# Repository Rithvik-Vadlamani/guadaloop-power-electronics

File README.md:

# Guadaloop power electronics

Selected power electronics designs from my work on Guadaloop. This repository collects editable schematics and PCB layouts so the designs can be reviewed without digging through unrelated project files.

| Design | What it covers | Files |
| --- | --- | --- |
| Levitation H-bridge | A nominal 60 V bidirectional coil-driver channel, including gate driving and current sensing. | [Design and review notes](levitation-hbridge/README.md) |
| 60 V to 24 V buck converter | A buck-converter design with a 10 A output target. | [Editable design](buck-60v-24v/) |
| Medium-voltage board, Rev F1 | A compact prototype power-board revision with revised inductance, compensation, and thermal copper. | [Design notes](medium-voltage-revf1/README.md) |

These are engineering designs and review packages. Their voltage/current targets are design requirements; the included files do not establish measured hardware performance.

My broader team work includes power distribution, PCB assembly, and enclosure work. This repository contains the design files located for this publication. It does not include every team design or claim sole authorship of collaborative work.

For my wireless power transfer models and results, see [the separate wireless power repository](https://github.com/Rithvik-Vadlamani/guadaloop-wireless-power-transfer).

## Open the designs

Use KiCad with the standard symbol and footprint libraries installed. Each folder contains its own project and local library tables. Start with the `.kicad_pro` file. Some projects were saved with KiCad 10; the levitation design requires KiCad 10.0.3 or later.

Saved review results describe the revision and assumptions recorded in each package. Native design files are the source of truth. No fabrication or hardware testing was performed as part of publishing this repository.

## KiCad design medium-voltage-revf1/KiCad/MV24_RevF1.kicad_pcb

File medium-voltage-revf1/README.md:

# MV24 Rev F1 — compact prototype candidate

Rev F1 implements the agreed minimal-change revisions to Rev F, except precharge. It preserves the original CSD19532Q5BT MOSFETs, all component positions, connector positions, mounting holes and board outline. Rev F is preserved separately. No board has been built or tested.

## What changed

| Item | Rev F | Rev F1 | Purpose |
|---|---|---|---|
| L1 | 10 µH, CPRX3231L-100MC | 15 µH, CPRX3231L-150MC | Coordinate inductance with the reduced switching frequency to limit ripple. Same package family and placement; revised terminal slots. |
| R6 | 75 kΩ | 100 kΩ, RT0805BRD07100KL | Reduce nominal switching frequency from approximately 133 kHz to 100 kHz, reducing gate-drive demand and frequency-dependent losses. |
| R10 | 6.81 kΩ | 8.2 kΩ, RC0805FR-078K2L | Retune compensation for the revised power stage. C26 remains 3.3 nF. |
| Copper | 35/15.2/15.2/35 µm | 70/35/35/70 µm | Improve conduction and heat spreading without enlarging the board. |
| MOSFET cooling paths | Original copper and vias | Local VIN copper extended, small bottom SW island, 37 additional thermal vias | Transfer heat away from the existing MOSFET packages. |
| Surface finish | OSP | ENIG | Flat assembly surface compatible with the specified filled-and-capped in-pad via process. |

There are still **51 fitted electronic/connector parts: three substitutions, zero added fitted parts**. The 63 PCB footprints also include six test points, four mounting holes and two unpopulated snubber positions. Vias are board features, not additional BOM components. External cooling equipment is separate from that count.

## Files

- `KiCad/MV24_RevF1.kicad_pro`: native editable project with local libraries/models.
- `Procurement/BOM.csv`: updated exact-part prototype BOM. Prices and availability have not been refreshed; this is not a purchase-ready quotation.
- `Documentation/Board.png` and `Documentation/Schematic.png`: reviewed previews.
- `Documentation/Engineering-notes.md`: design rationale, calculation scope and remaining uncertainties.
- `Documentation/Fabrication-and-test.md`: required PCB process, cooling fixture and staged test plan.
- `Verification/final-native/`: final ERC, DRC, native netlists and independent connectivity reports.
- `Verification/final-audit.json`: unchanged-layout/MOSFET/BOM comparison and report freshness checks.
- `Manufacturing/`: reviewed four-layer Gerbers, plated/non-plated drills, fabrication requirements and a selective filled-via map.
- `Assembly/`: reconciled 51-part BOM/placements, labeled assembly drawing and populated-variant stencil artwork with process-review instructions.

## Status

Native KiCad 10.0.3 ERC and DRC pass with no reported violations, unconnected items or schematic parity findings. Independent schematic/PCB connectivity and pad-map checks pass. All 154 tracked baseline files are unchanged. These checks establish consistency and routing-rule compliance, not power performance or safety qualification.

The averaged loop screen supports the chosen compensation as a prototype candidate. Thermal screening still indicates substantial heating and sensitivity to airflow/model resolution. **Continuous 24 V / 20 A operation is a design target, not an established rating.**

Precharge and the associated battery connection/fusing decisions are intentionally deferred as a separate scope. Do not directly hot-plug the battery into this candidate. The board-only fabrication/assembly handoff is prepared independently for fabricator DFM and a supervised bench prototype; it does not wait for a battery-interface redesign. Vendor process acceptance and assembler stencil/orientation review remain required before ordering. No hardware-performance or battery-use release is implied.

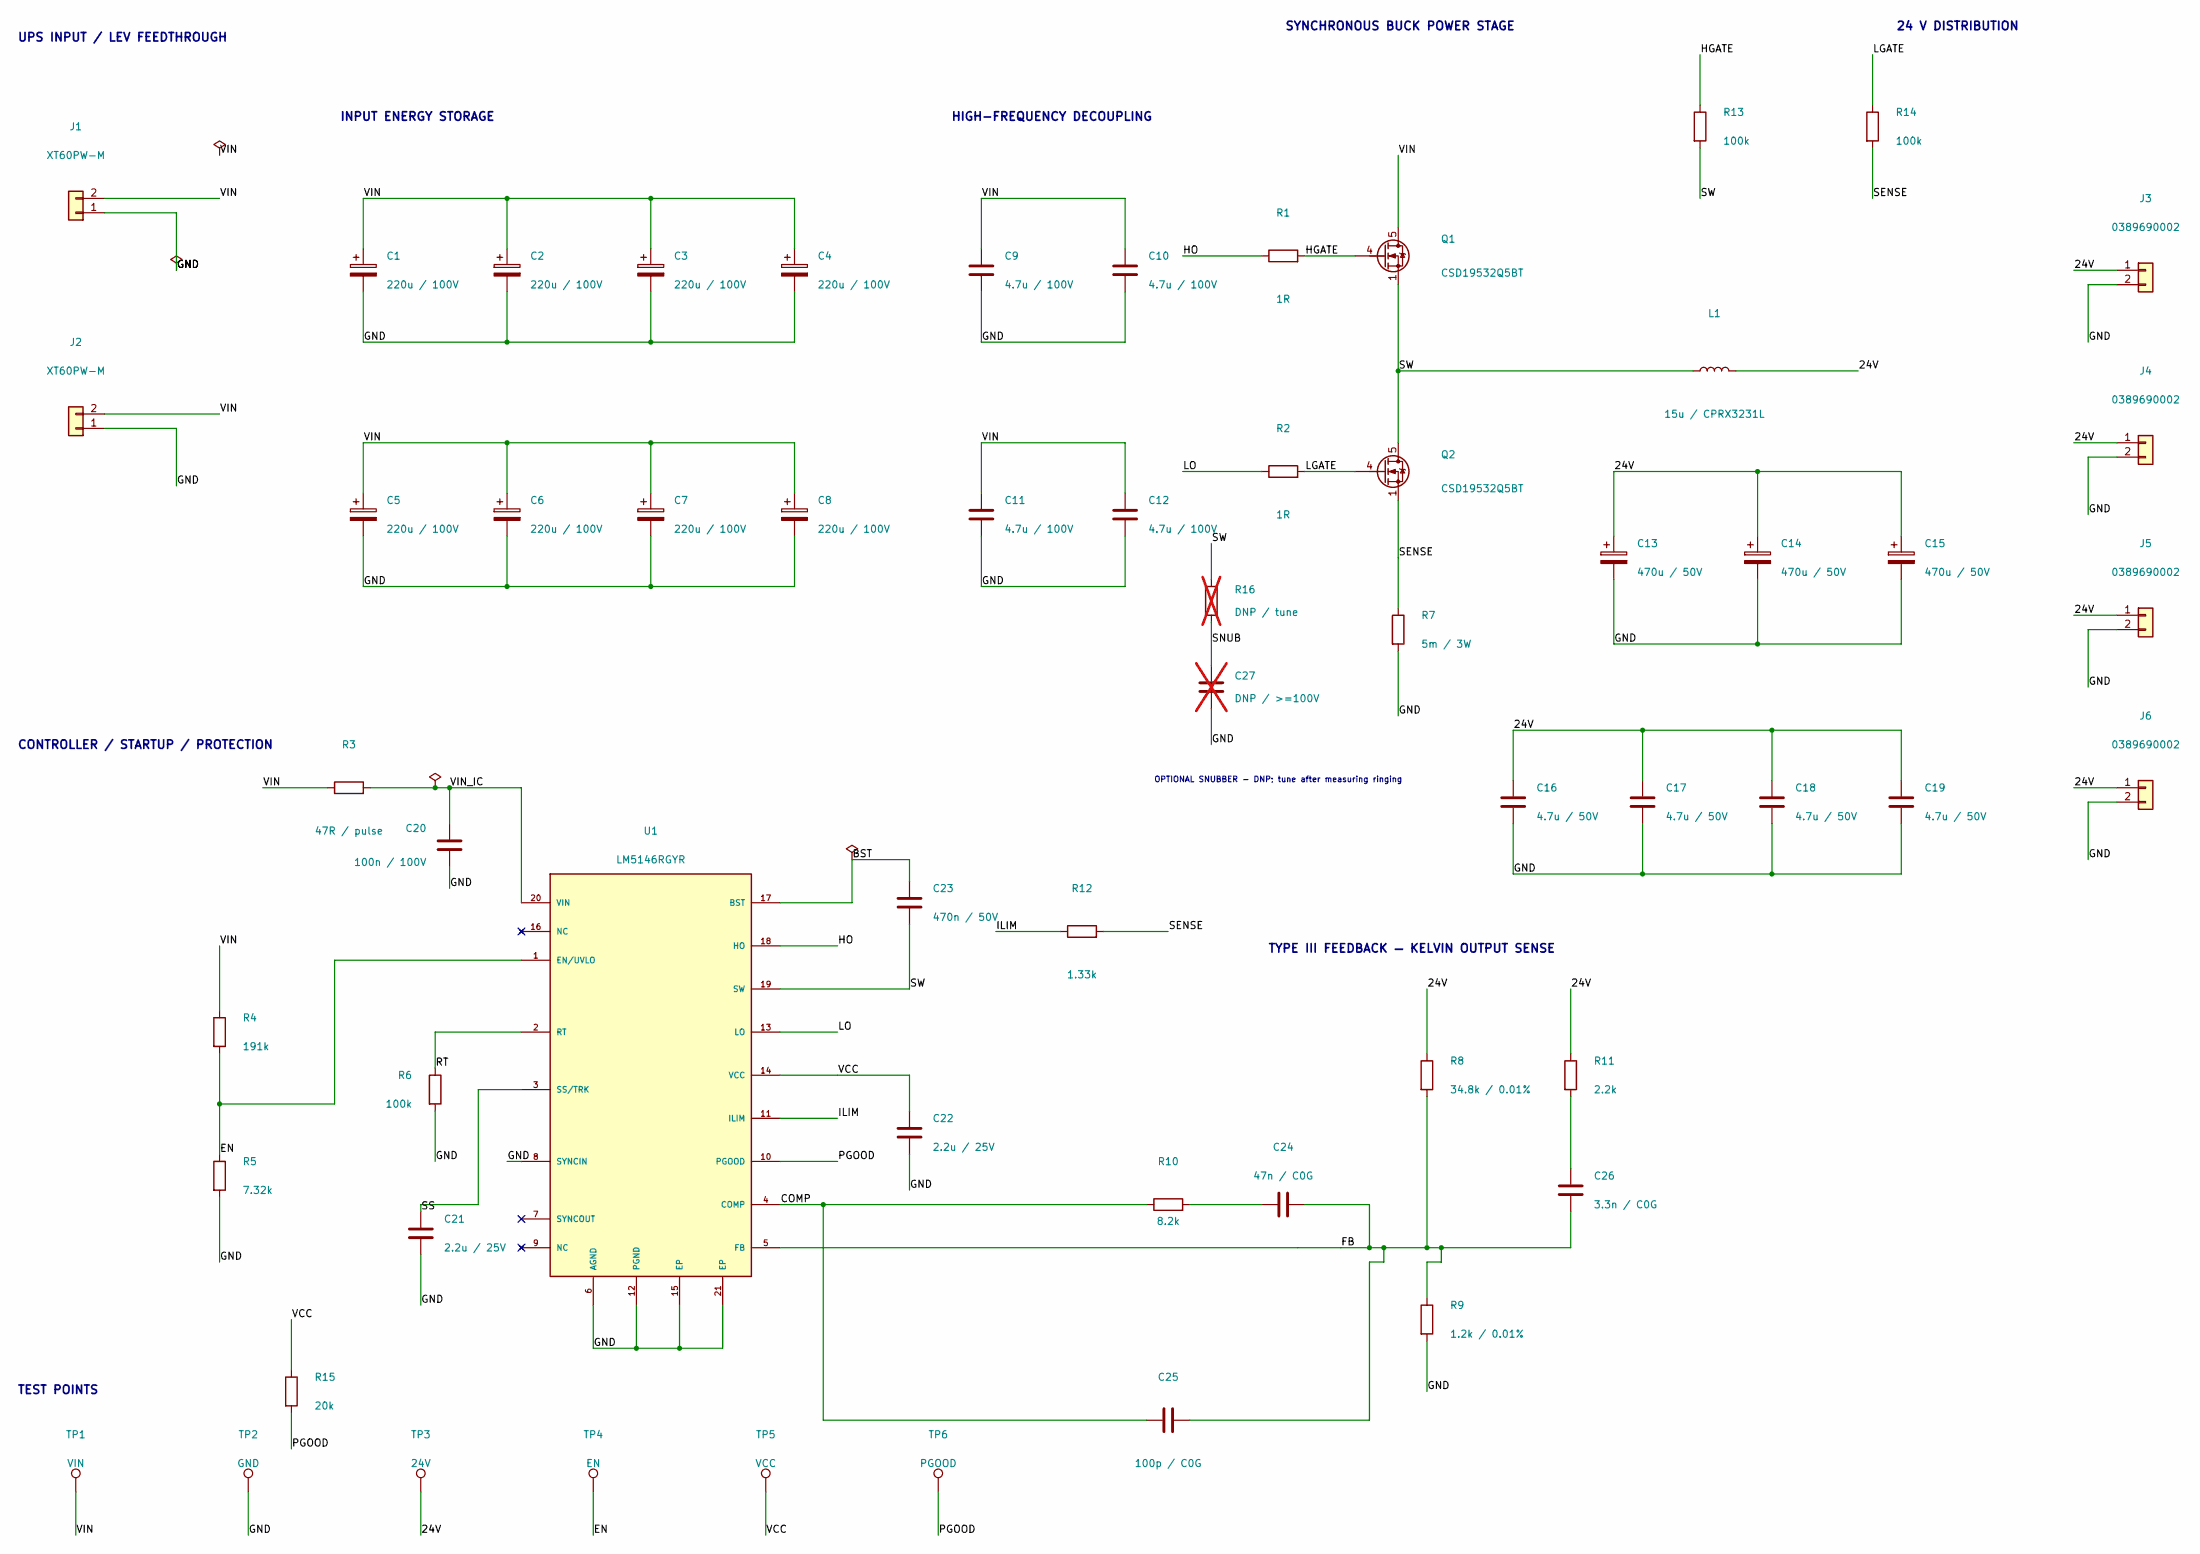
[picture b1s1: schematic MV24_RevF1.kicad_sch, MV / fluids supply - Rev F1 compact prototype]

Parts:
C1, C2, C3, C4, C5, C6, C7, C8: 220u / 100V; CP_Radial_D12.5mm_P5.00mm; MPN EEU-FS2A221B
C9, C10, C11, C12: 4.7u / 100V; C_1812_4532Metric; MPN KGM43JR72A475KV
C13, C14, C15: 470u / 50V; CP_Radial_D12.5mm_P5.00mm; MPN EEU-FR1H471B
C16, C17, C18, C19: 4.7u / 50V; C_1206_3216Metric; MPN GRM31CR71H475KA12L
C20: 100n / 100V; C_0805_2012Metric; MPN C0805C104K1RACTU
C21, C22: 2.2u / 25V; C_0805_2012Metric; MPN C0805C225K3RACTU
C23: 470n / 50V; C_0805_2012Metric; MPN C0805C474K5RACTU
C24: 47n / C0G; C_1206_3216Metric; MPN C1206C473J5GACTU
C25: 100p / C0G; C_0805_2012Metric; MPN C0805C101J5GACTU
C26: 3.3n / C0G; C_0805_2012Metric; MPN C0805C332J5GACTU
C27: DNP / >=100V; C_1206_3216Metric; not fitted
J1, J2: XT60PW-M; AMASS_XT60PW-M_1x02_P7.20mm_Horizontal; MPN XT60PW-M
J3, J4, J5, J6: 0389690002; Molex_0389690002; MPN 0389690002
L1: 15u / CPRX3231L; CODACA_CPRX3231L_150MC; MPN CPRX3231L-150MC
Q1, Q2: CSD19532Q5BT; TI_Q5B_5x6; MPN CSD19532Q5BT
R1, R2: 1R; R_0805_2012Metric; MPN RC0805FR-071RL
R3: 47R / pulse; R_0805_2012Metric; MPN CRCW080547R0FKEAHP
R4: 191k; R_0805_2012Metric; MPN RC0805FR-07191KL
R5: 7.32k; R_0805_2012Metric; MPN RC0805FR-077K32L
R6: 100k; R_0805_2012Metric; MPN RT0805BRD07100KL
R7: 5m / 3W; Bourns_CRE2512_R005; MPN CRE2512-FZ-R005E-3
R8: 34.8k / 0.01%; R_0805_2012Metric; MPN RT0805LRA0734K8L
R9: 1.2k / 0.01%; R_0805_2012Metric; MPN RT0805LRA071K2L
R10: 8.2k; R_0805_2012Metric; MPN RC0805FR-078K2L
R11: 2.2k; R_0805_2012Metric; MPN RC0805FR-072K2L
R12: 1.33k; R_0805_2012Metric; MPN RT0805BRD071K33L
R13, R14: 100k; R_0805_2012Metric; MPN RC0805FR-07100KL
R15: 20k; R_0805_2012Metric; MPN RC0805FR-0720KL
R16: DNP / tune; R_1206_3216Metric; not fitted
TP1: VIN; TestPoint_Pad_D2.0mm
TP2: GND; TestPoint_Pad_D2.0mm
TP3: 24V; TestPoint_Pad_D2.0mm
TP4: EN; TestPoint_Pad_D2.0mm
TP5: VCC; TestPoint_Pad_D2.0mm
TP6: PGOOD; TestPoint_Pad_D2.0mm
U1: LM5146RGYR; TI_RGY0020B; MPN LM5146RGYR

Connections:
/24V: C13.1, C14.1, C15.1, C16.1, C17.1, C18.1, C19.1, J3.1, J4.1, J5.1, J6.1, L1.2, R8.1, R11.1, TP3.1
/BST: C23.1, U1.17 (BST)
/COMP: C25.1, R10.1, U1.4 (COMP)
/EN: R4.2, R5.1, TP4.1, U1.1 (EN/UVLO)
/FB: C24.2, C25.2, C26.2, R8.2, R9.1, U1.5 (FB)
/GND: C1.2, C2.2, C3.2, C4.2, C5.2, C6.2, C7.2, C8.2, C9.2, C10.2, C11.2, C12.2, C13.2, C14.2, C15.2, C16.2, C17.2, C18.2, C19.2, C20.2, C21.2, C22.2, C27.2, J1.1, J2.1, J3.2, J4.2, J5.2, J6.2, R5.2, R6.2, R7.2, R9.2, TP2.1, U1.6 (AGND), U1.8 (SYNCIN), U1.12 (PGND), U1.15 (EP), U1.21 (EP)
/HGATE: Q1.4 (G), R1.2, R13.1
/HO: R1.1, U1.18 (HO)
/ILIM: R12.1, U1.11 (ILIM)
/LGATE: Q2.4 (G), R2.2, R14.1
/LO: R2.1, U1.13 (LO)
/PGOOD: R15.2, TP6.1, U1.10 (PGOOD)
/RT: R6.1, U1.2 (RT)
/SENSE: Q2.1 (S), Q2.2 (S), Q2.3 (S), R7.1, R12.2, R14.2
/SNUB: C27.1, R16.2
/SS: C21.1, U1.3 (SS/TRK)
/SW: C23.2, L1.1, Q1.1 (S), Q1.2 (S), Q1.3 (S), Q2.5 (D), R13.2, R16.1, U1.19 (SW)
/VCC: C22.1, R15.1, TP5.1, U1.14 (VCC)
/VIN: C1.1, C2.1, C3.1, C4.1, C5.1, C6.1, C7.1, C8.1, C9.1, C10.1, C11.1, C12.1, J1.2, J2.2, Q1.5 (D), R3.1, R4.1, TP1.1
/VIN_IC: C20.1, R3.2, U1.20 (VIN)
unnamed: C24.1, R10.2
unnamed: C26.1, R11.2

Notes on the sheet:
UPS INPUT / LEV FEEDTHROUGH
INPUT ENERGY STORAGE
HIGH-FREQUENCY DECOUPLING
SYNCHRONOUS BUCK POWER STAGE
24 V DISTRIBUTION
CONTROLLER / STARTUP / PROTECTION
TYPE III FEEDBACK — KELVIN OUTPUT SENSE
TEST POINTS
OPTIONAL SNUBBER - DNP; tune after measuring ringing

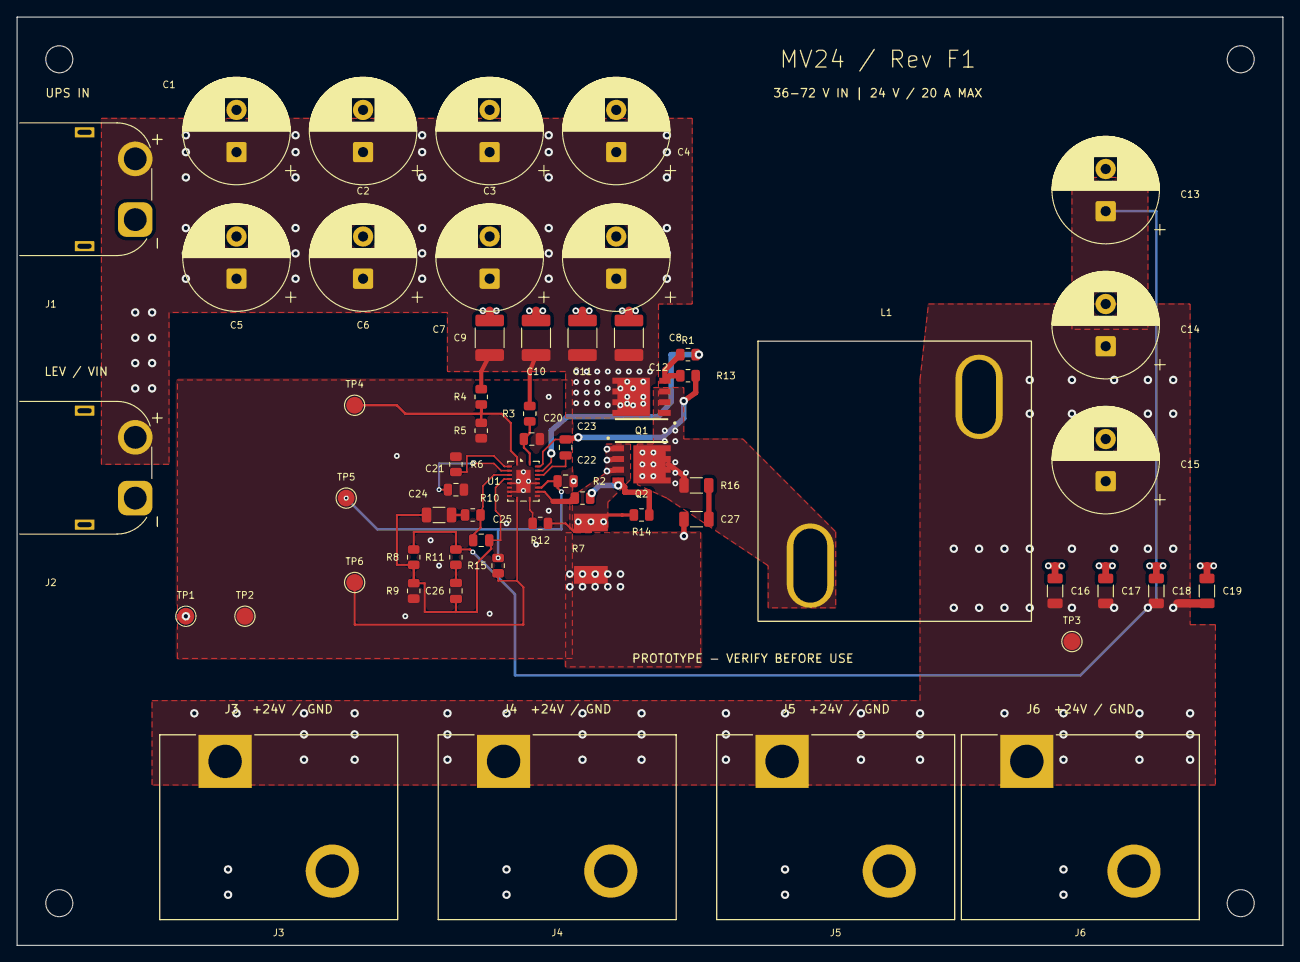
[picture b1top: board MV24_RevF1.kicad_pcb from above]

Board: 4 copper layers, 150.0 x 110.0 mm, 63 parts (0 on the bottom side), 22 nets.

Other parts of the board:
H1, H2, H3, H4: M3 clearance; MountingHole_3.2mm_M3

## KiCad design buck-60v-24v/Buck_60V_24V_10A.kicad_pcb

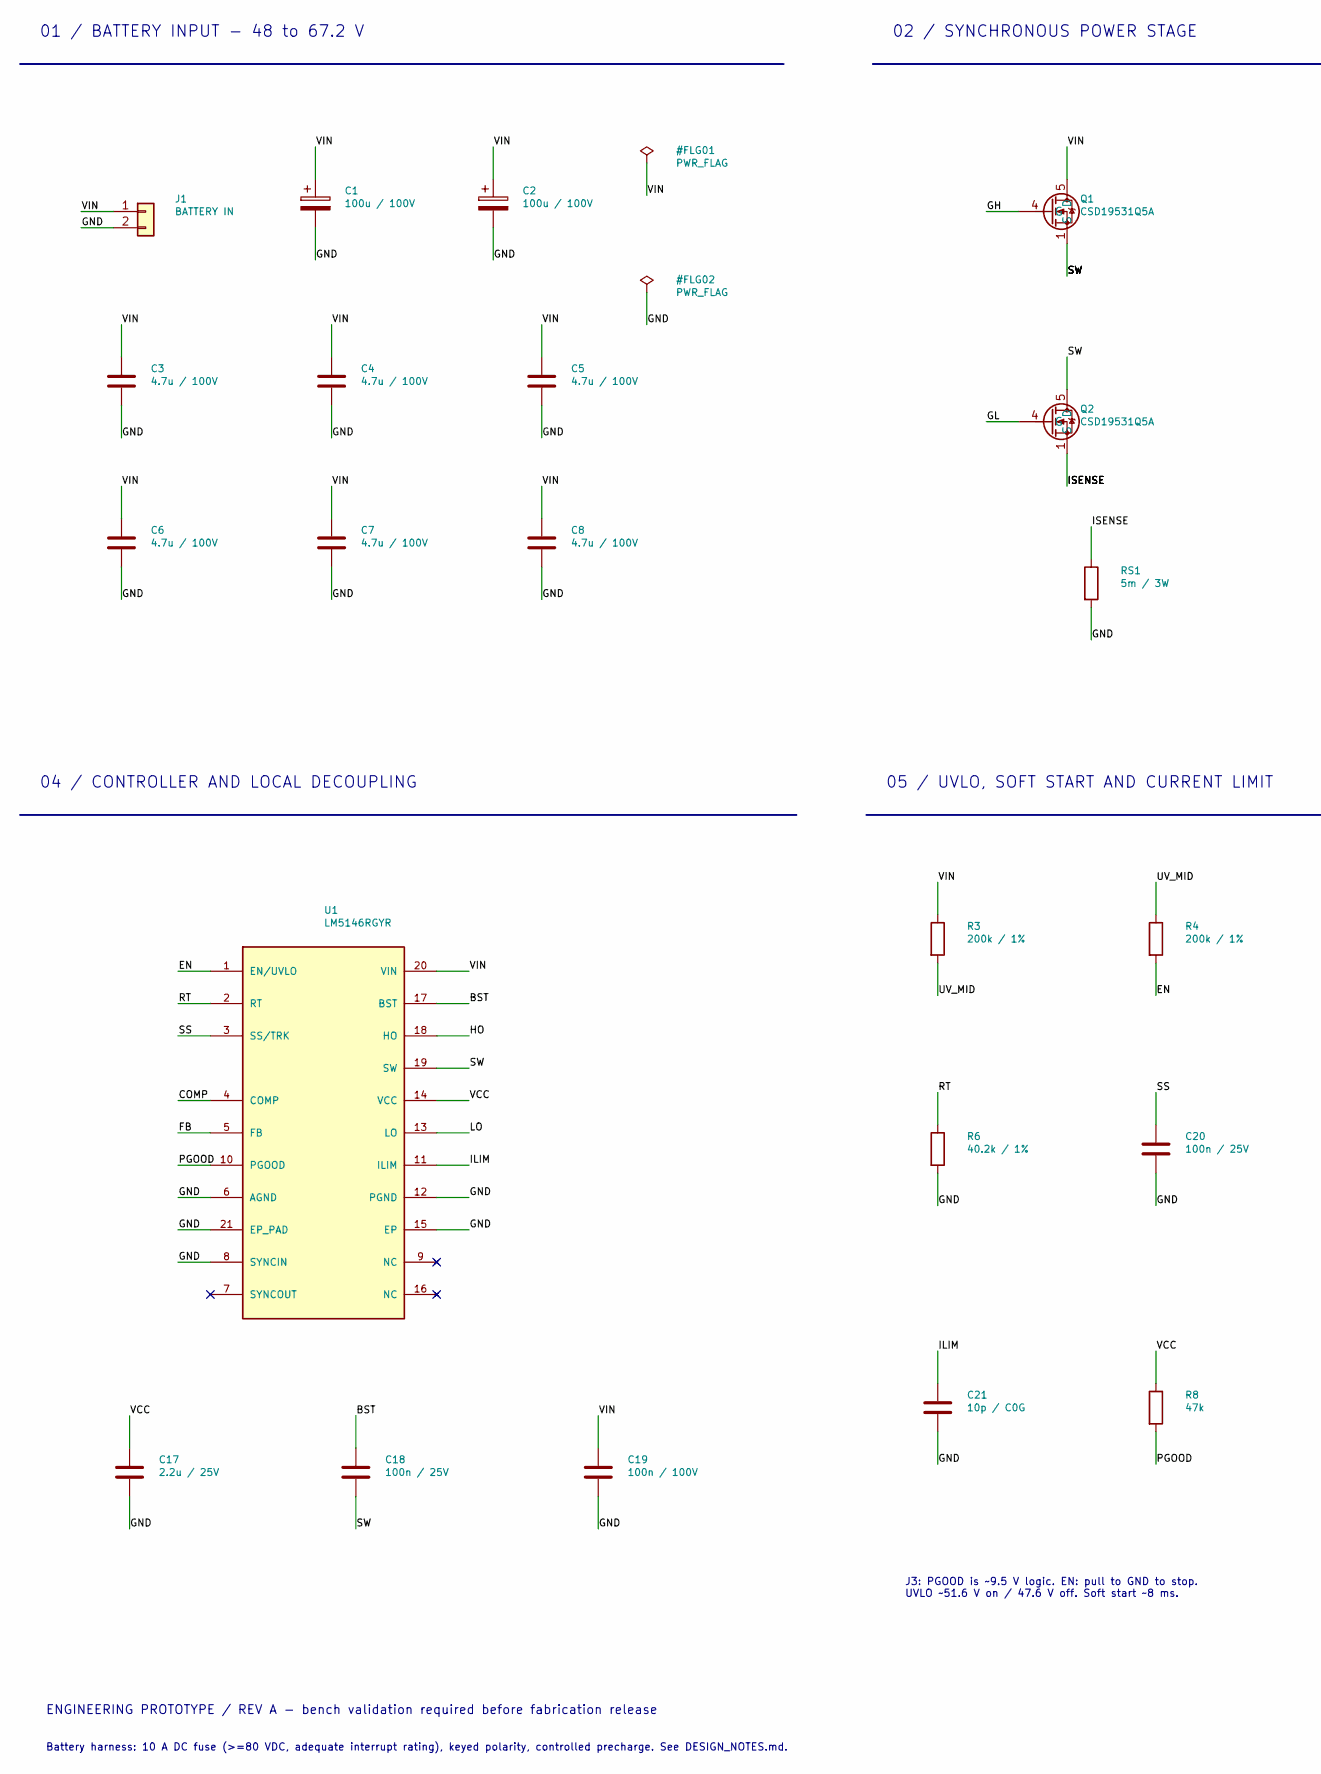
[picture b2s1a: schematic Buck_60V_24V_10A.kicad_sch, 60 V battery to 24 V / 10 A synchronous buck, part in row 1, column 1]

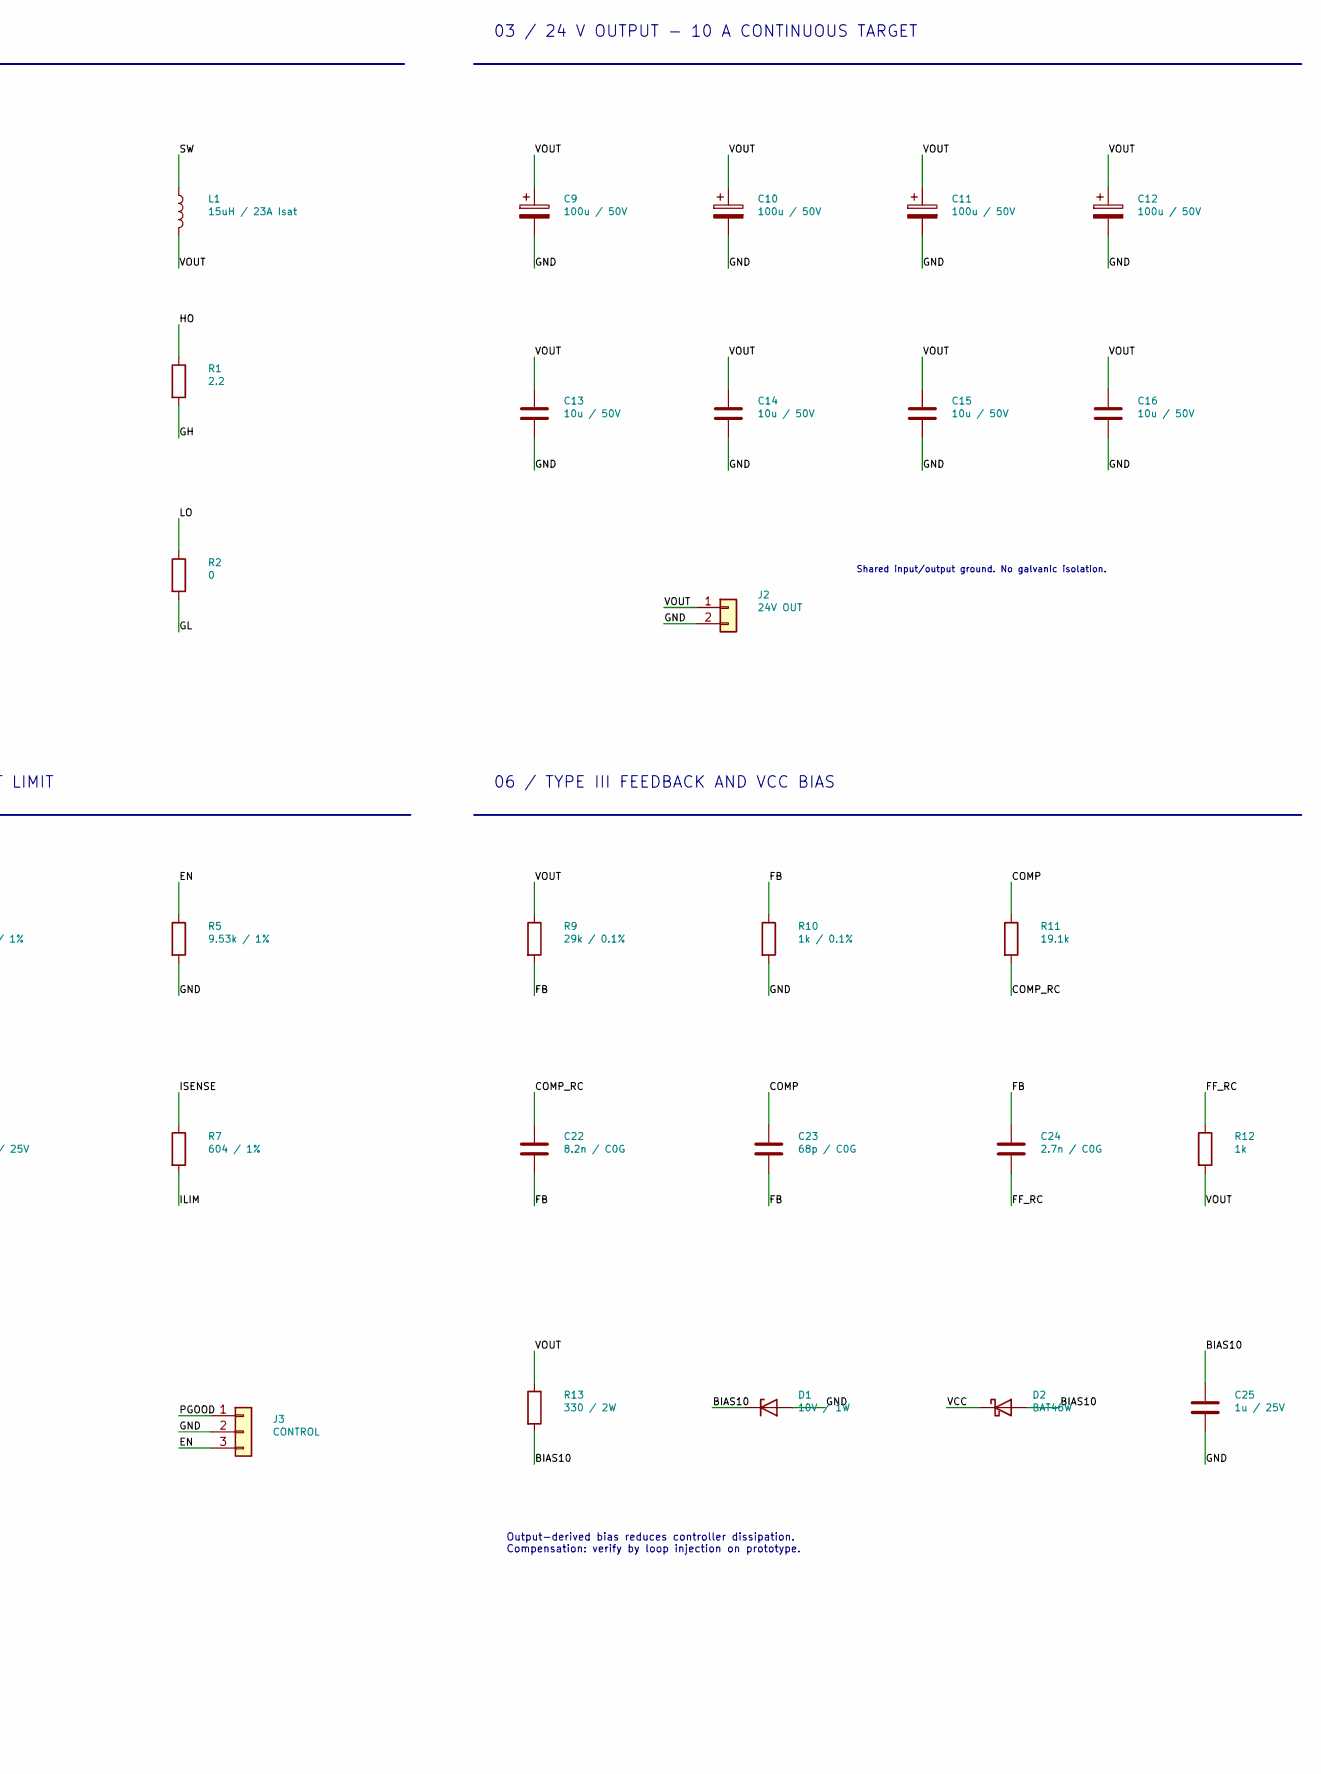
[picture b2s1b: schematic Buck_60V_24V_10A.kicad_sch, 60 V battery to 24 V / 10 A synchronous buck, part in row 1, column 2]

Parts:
C1, C2: 100u / 100V; CP_Radial_D10.0mm_P5.00mm; MPN EEU-FR2A101
C3, C4, C5, C6, C7, C8: 4.7u / 100V; C_1210_3225Metric; MPN CGA6M3X7S2A475K200AB
C9, C10, C11, C12: 100u / 50V; C_Elec_10x10.2; MPN EEH-ZE1H101P
C13, C14, C15, C16: 10u / 50V; C_1210_3225Metric; MPN GRM32ER71H106KA12L
C17: 2.2u / 25V; C_0805_2012Metric; MPN GRM21BR71E225KA73L
C18, C20: 100n / 25V; C_0603_1608Metric; MPN GRM188R71E104KA01D
C19: 100n / 100V; C_0805_2012Metric; MPN GRM21BR72A104KAC4L
C21: 10p / C0G; C_0603_1608Metric; MPN GRM1885C1H100JA01D
C22: 8.2n / C0G; C_0603_1608Metric; MPN GRM1885C1H822JA01D
C23: 68p / C0G; C_0603_1608Metric; MPN GRM1885C1H680JA01D
C24: 2.7n / C0G; C_0603_1608Metric; MPN GRM1885C1H272JA01D
C25: 1u / 25V; C_0805_2012Metric; MPN GRM21BR71E105KA99L
D1: 10V / 1W; D_SMA; MPN SMAZ10-13-F
D2: BAT46W; D_SOD-123; MPN BAT46W-7-F
J1: BATTERY IN; AMASS_XT60PW-M_1x02_P7.20mm_Horizontal; MPN XT60PW-M
J2: 24V OUT; AMASS_XT60PW-F_1x02_P7.20mm_Horizontal; MPN XT60PW-F
J3: CONTROL; PinHeader_1x03_P2.54mm_Vertical; MPN Pin header 1x3 2.54mm
L1: 15uH / 23A Isat; L_Coilcraft_XAL1510-153; MPN XAL1510-153MED
Q1, Q2: CSD19531Q5A; TDSON-8-1; MPN CSD19531Q5A
R1: 2.2; R_0603_1608Metric; MPN RC0603FR-072R2L
R2: 0; R_0603_1608Metric; MPN RC0603JR-070RL
R3, R4: 200k / 1%; R_0603_1608Metric; MPN RC0603FR-07200KL
R5: 9.53k / 1%; R_0603_1608Metric; MPN RC0603FR-079K53L
R6: 40.2k / 1%; R_0603_1608Metric; MPN RC0603FR-0740K2L
R7: 604 / 1%; R_0603_1608Metric; MPN RC0603FR-07604RL
R8: 47k; R_0603_1608Metric; MPN RC0603FR-0747KL
R9: 29k / 0.1%; R_0603_1608Metric; MPN TNPW060329K0BEEA
R10: 1k / 0.1%; R_0603_1608Metric; MPN TNPW06031K00BEEA
R11: 19.1k; R_0603_1608Metric; MPN RC0603FR-0719K1L
R12: 1k; R_0603_1608Metric; MPN RC0603FR-071KL
R13: 330 / 2W; R_2512_6332Metric; MPN CRCW2512330RJNEGHP
RS1: 5m / 3W; R_2512_6332Metric; MPN WSLP25125L000FEA
U1: LM5146RGYR; LM5146_RGY0020B; MPN LM5146RGYR

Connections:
BIAS10: C25.1, D1.1 (K), D2.2 (A), R13.2
BST: C18.1, U1.17 (BST)
COMP: C23.1, R11.1, U1.4 (COMP)
COMP_RC: C22.1, R11.2
EN: J3.3, R4.2, R5.1, U1.1 (EN/UVLO)
FB: C22.2, C23.2, C24.1, R9.2, R10.1, U1.5 (FB)
FF_RC: C24.2, R12.1
GH: Q1.4 (G), R1.2
GL: Q2.4 (G), R2.2
GND: C1.2, C2.2, C3.2, C4.2, C5.2, C6.2, C7.2, C8.2, C9.2, C10.2, C11.2, C12.2, C13.2, C14.2, C15.2, C16.2, C17.2, C19.2, C20.2, C21.2, C25.2, D1.2 (A), J1.2, J2.2, J3.2, R5.2, R6.2, R10.2, RS1.2, U1.6 (AGND), U1.8 (SYNCIN), U1.12 (PGND), U1.15 (EP), U1.21 (EP_PAD)
HO: R1.1, U1.18 (HO)
ILIM: C21.1, R7.2, U1.11 (ILIM)
ISENSE: Q2.1 (S), Q2.2 (S), Q2.3 (S), R7.1, RS1.1
LO: R2.1, U1.13 (LO)
PGOOD: J3.1, R8.2, U1.10 (PGOOD)
RT: R6.1, U1.2 (RT)
SS: C20.1, U1.3 (SS/TRK)
SW: C18.2, L1.1, Q1.1 (S), Q1.2 (S), Q1.3 (S), Q2.5 (D), U1.19 (SW)
UV_MID: R3.2, R4.1
VCC: C17.1, D2.1 (K), R8.1, U1.14 (VCC)
VIN: C1.1, C2.1, C3.1, C4.1, C5.1, C6.1, C7.1, C8.1, C19.1, J1.1, Q1.5 (D), R3.1, U1.20 (VIN)
VOUT: C9.1, C10.1, C11.1, C12.1, C13.1, C14.1, C15.1, C16.1, J2.1, L1.2, R9.1, R12.2, R13.1

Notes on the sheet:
06 / TYPE III FEEDBACK AND VCC BIAS
ENGINEERING PROTOTYPE / REV A - bench validation required before fabrication release
01 / BATTERY INPUT - 48 to 67.2 V
04 / CONTROLLER AND LOCAL DECOUPLING
Output-derived bias reduces controller dissipation. Compensation: verify by loop injection on prototype.
03 / 24 V OUTPUT - 10 A CONTINUOUS TARGET
02 / SYNCHRONOUS POWER STAGE
Shared input/output ground. No galvanic isolation.
J3: PGOOD is ~9.5 V logic. EN: pull to GND to stop. UVLO ~51.6 V on / 47.6 V off. Soft start ~8 ms.
05 / UVLO, SOFT START AND CURRENT LIMIT
Battery harness: 10 A DC fuse (>=80 VDC, adequate interrupt rating), keyed polarity, controlled precharge. See DESIGN_NOTES.md.

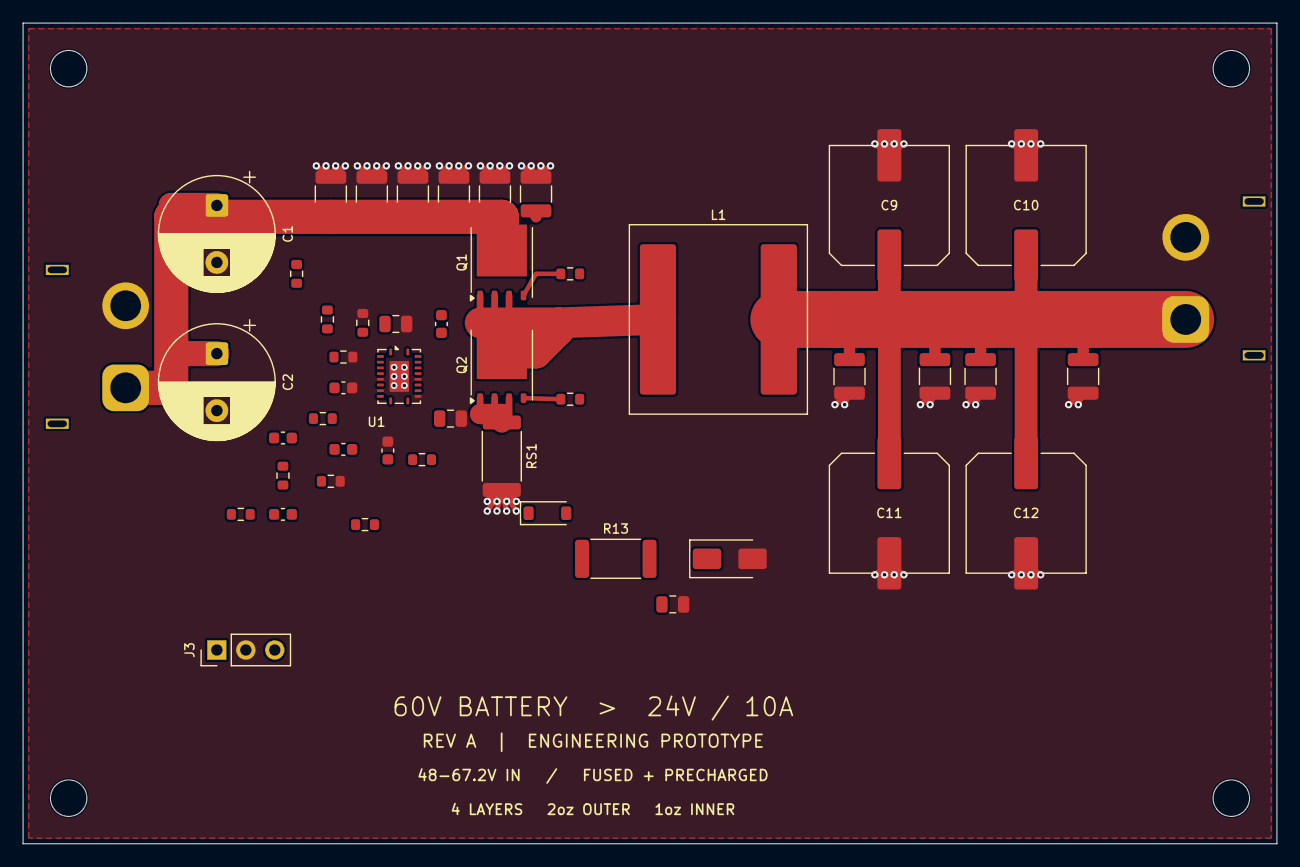
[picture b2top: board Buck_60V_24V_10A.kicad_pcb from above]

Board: 4 copper layers, 110.0 x 72.0 mm, 52 parts (0 on the bottom side), 22 nets.

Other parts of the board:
H1, H2, H3, H4: MountingHole_3.2mm_M3

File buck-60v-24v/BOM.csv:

Reference,Value,MPN,Footprint,Notes
J1,BATTERY IN,XT60PW-M,Connector_AMASS:AMASS_XT60PW-M_1x02_P7.20mm_Horizontal,
C1,100u / 100V,EEU-FR2A101,Capacitor_THT:CP_Radial_D10.0mm_P5.00mm,
C2,100u / 100V,EEU-FR2A101,Capacitor_THT:CP_Radial_D10.0mm_P5.00mm,
C3,4.7u / 100V,CGA6M3X7S2A475K200AB,Capacitor_SMD:C_1210_3225Metric,
C4,4.7u / 100V,CGA6M3X7S2A475K200AB,Capacitor_SMD:C_1210_3225Metric,
C5,4.7u / 100V,CGA6M3X7S2A475K200AB,Capacitor_SMD:C_1210_3225Metric,
C6,4.7u / 100V,CGA6M3X7S2A475K200AB,Capacitor_SMD:C_1210_3225Metric,
C7,4.7u / 100V,CGA6M3X7S2A475K200AB,Capacitor_SMD:C_1210_3225Metric,
C8,4.7u / 100V,CGA6M3X7S2A475K200AB,Capacitor_SMD:C_1210_3225Metric,
Q1,CSD19531Q5A,CSD19531Q5A,Package_TO_SOT_SMD:TDSON-8-1,
Q2,CSD19531Q5A,CSD19531Q5A,Package_TO_SOT_SMD:TDSON-8-1,
RS1,5m / 3W,WSLP25125L000FEA,Resistor_SMD:R_2512_6332Metric,
L1,15uH / 23A Isat,XAL1510-153MED,Inductor_SMD:L_Coilcraft_XAL1510-153,
R1,2.2,RC0603FR-072R2L,Resistor_SMD:R_0603_1608Metric,
R2,0,RC0603JR-070RL,Resistor_SMD:R_0603_1608Metric,
C9,100u / 50V,EEH-ZE1H101P,Capacitor_SMD:C_Elec_10x10.2,
C10,100u / 50V,EEH-ZE1H101P,Capacitor_SMD:C_Elec_10x10.2,
C11,100u / 50V,EEH-ZE1H101P,Capacitor_SMD:C_Elec_10x10.2,
C12,100u / 50V,EEH-ZE1H101P,Capacitor_SMD:C_Elec_10x10.2,
C13,10u / 50V,GRM32ER71H106KA12L,Capacitor_SMD:C_1210_3225Metric,
C14,10u / 50V,GRM32ER71H106KA12L,Capacitor_SMD:C_1210_3225Metric,
C15,10u / 50V,GRM32ER71H106KA12L,Capacitor_SMD:C_1210_3225Metric,
C16,10u / 50V,GRM32ER71H106KA12L,Capacitor_SMD:C_1210_3225Metric,
J2,24V OUT,XT60PW-F,Connector_AMASS:AMASS_XT60PW-F_1x02_P7.20mm_Horizontal,
U1,LM5146RGYR,LM5146RGYR,Buck:LM5146_RGY0020B,https://www.ti.com/lit/ds/symlink/lm5146.pdf
C17,2.2u / 25V,GRM21BR71E225KA73L,Capacitor_SMD:C_0805_2012Metric,
C18,100n / 25V,GRM188R71E104KA01D,Capacitor_SMD:C_0603_1608Metric,
C19,100n / 100V,GRM21BR72A104KAC4L,Capacitor_SMD:C_0805_2012Metric,
R3,200k / 1%,RC0603FR-07200KL,Resistor_SMD:R_0603_1608Metric,
R4,200k / 1%,RC0603FR-07200KL,Resistor_SMD:R_0603_1608Metric,
R5,9.53k / 1%,RC0603FR-079K53L,Resistor_SMD:R_0603_1608Metric,
R6,40.2k / 1%,RC0603FR-0740K2L,Resistor_SMD:R_0603_1608Metric,
C20,100n / 25V,GRM188R71E104KA01D,Capacitor_SMD:C_0603_1608Metric,
R7,604 / 1%,RC0603FR-07604RL,Resistor_SMD:R_0603_1608Metric,
C21,10p / C0G,GRM1885C1H100JA01D,Capacitor_SMD:C_0603_1608Metric,
R8,47k,RC0603FR-0747KL,Resistor_SMD:R_0603_1608Metric,
J3,CONTROL,Pin header 1x3 2.54mm,Connector_PinHeader_2.54mm:PinHeader_1x03_P2.54mm_Vertical,
R9,29k / 0.1%,TNPW060329K0BEEA,Resistor_SMD:R_0603_1608Metric,
R10,1k / 0.1%,TNPW06031K00BEEA,Resistor_SMD:R_0603_1608Metric,
R11,19.1k,RC0603FR-0719K1L,Resistor_SMD:R_0603_1608Metric,
C22,8.2n / C0G,GRM1885C1H822JA01D,Capacitor_SMD:C_0603_1608Metric,
C23,68p / C0G,GRM1885C1H680JA01D,Capacitor_SMD:C_0603_1608Metric,
C24,2.7n / C0G,GRM1885C1H272JA01D,Capacitor_SMD:C_0603_1608Metric,
R12,1k,RC0603FR-071KL,Resistor_SMD:R_0603_1608Metric,
R13,330 / 2W,CRCW2512330RJNEGHP,Resistor_SMD:R_2512_6332Metric,
D1,10V / 1W,SMAZ10-13-F,Diode_SMD:D_SMA,
D2,BAT46W,BAT46W-7-F,Diode_SMD:D_SOD-123,
C25,1u / 25V,GRM21BR71E105KA99L,Capacitor_SMD:C_0805_2012Metric,
